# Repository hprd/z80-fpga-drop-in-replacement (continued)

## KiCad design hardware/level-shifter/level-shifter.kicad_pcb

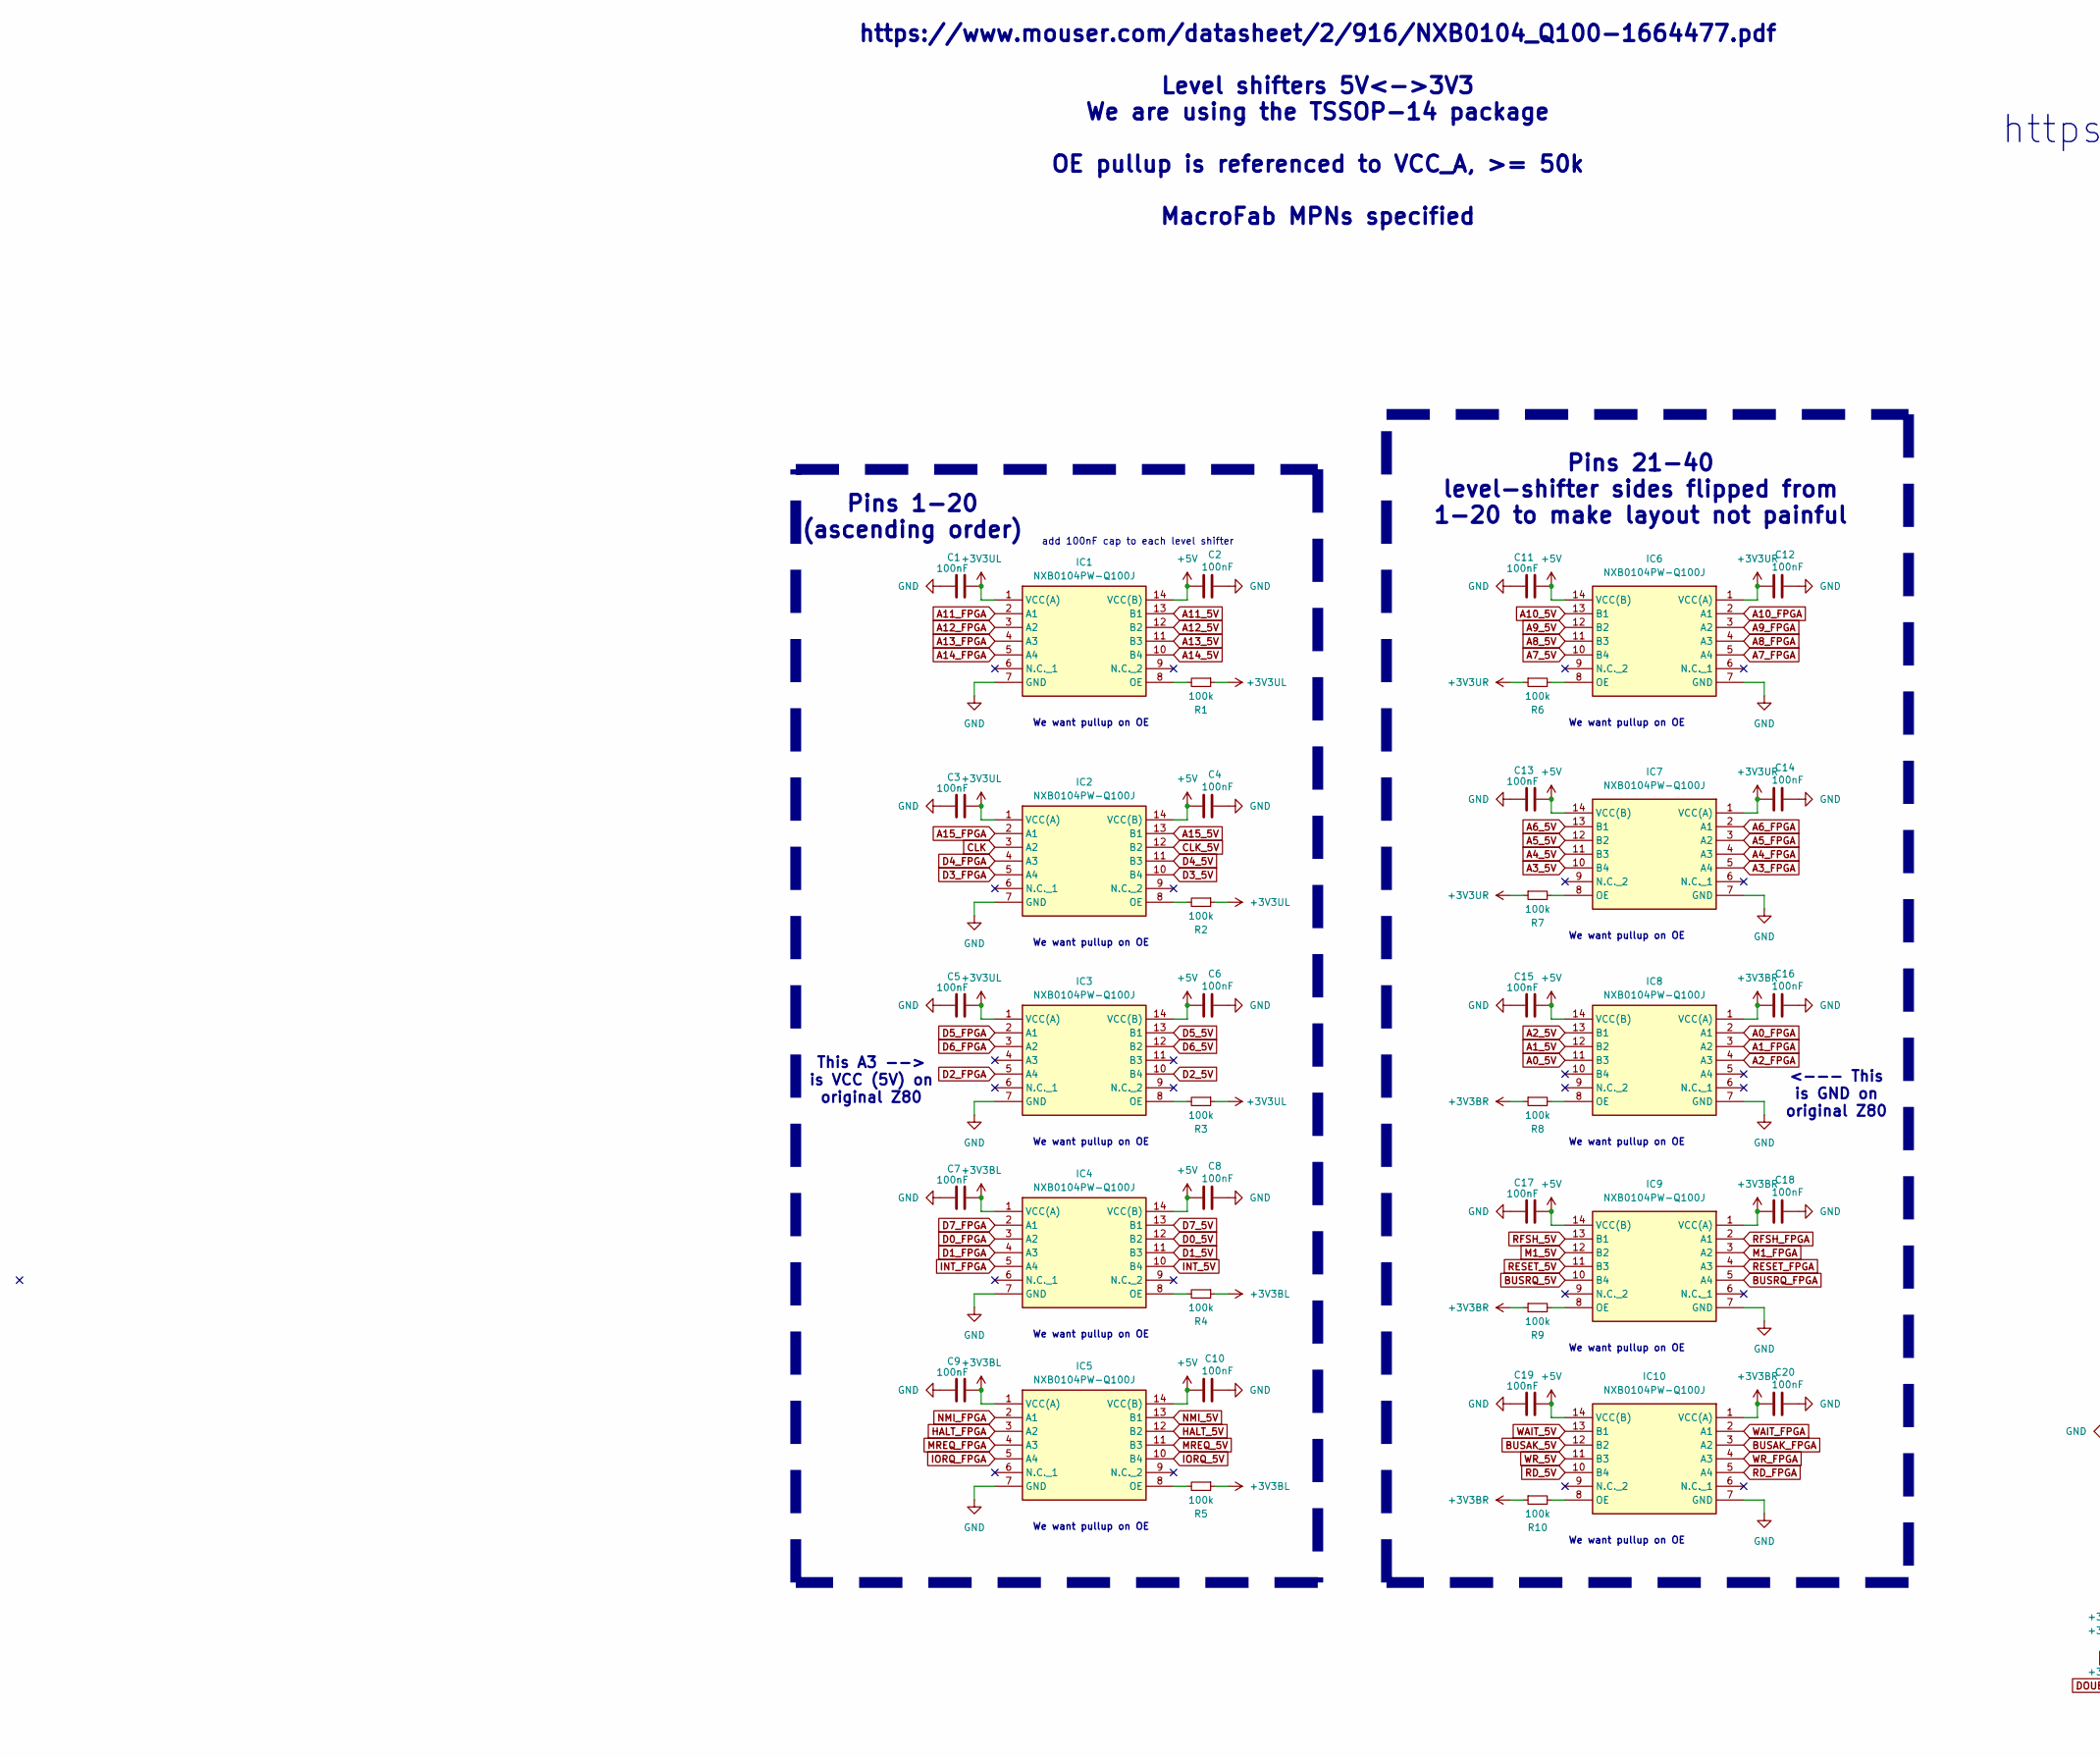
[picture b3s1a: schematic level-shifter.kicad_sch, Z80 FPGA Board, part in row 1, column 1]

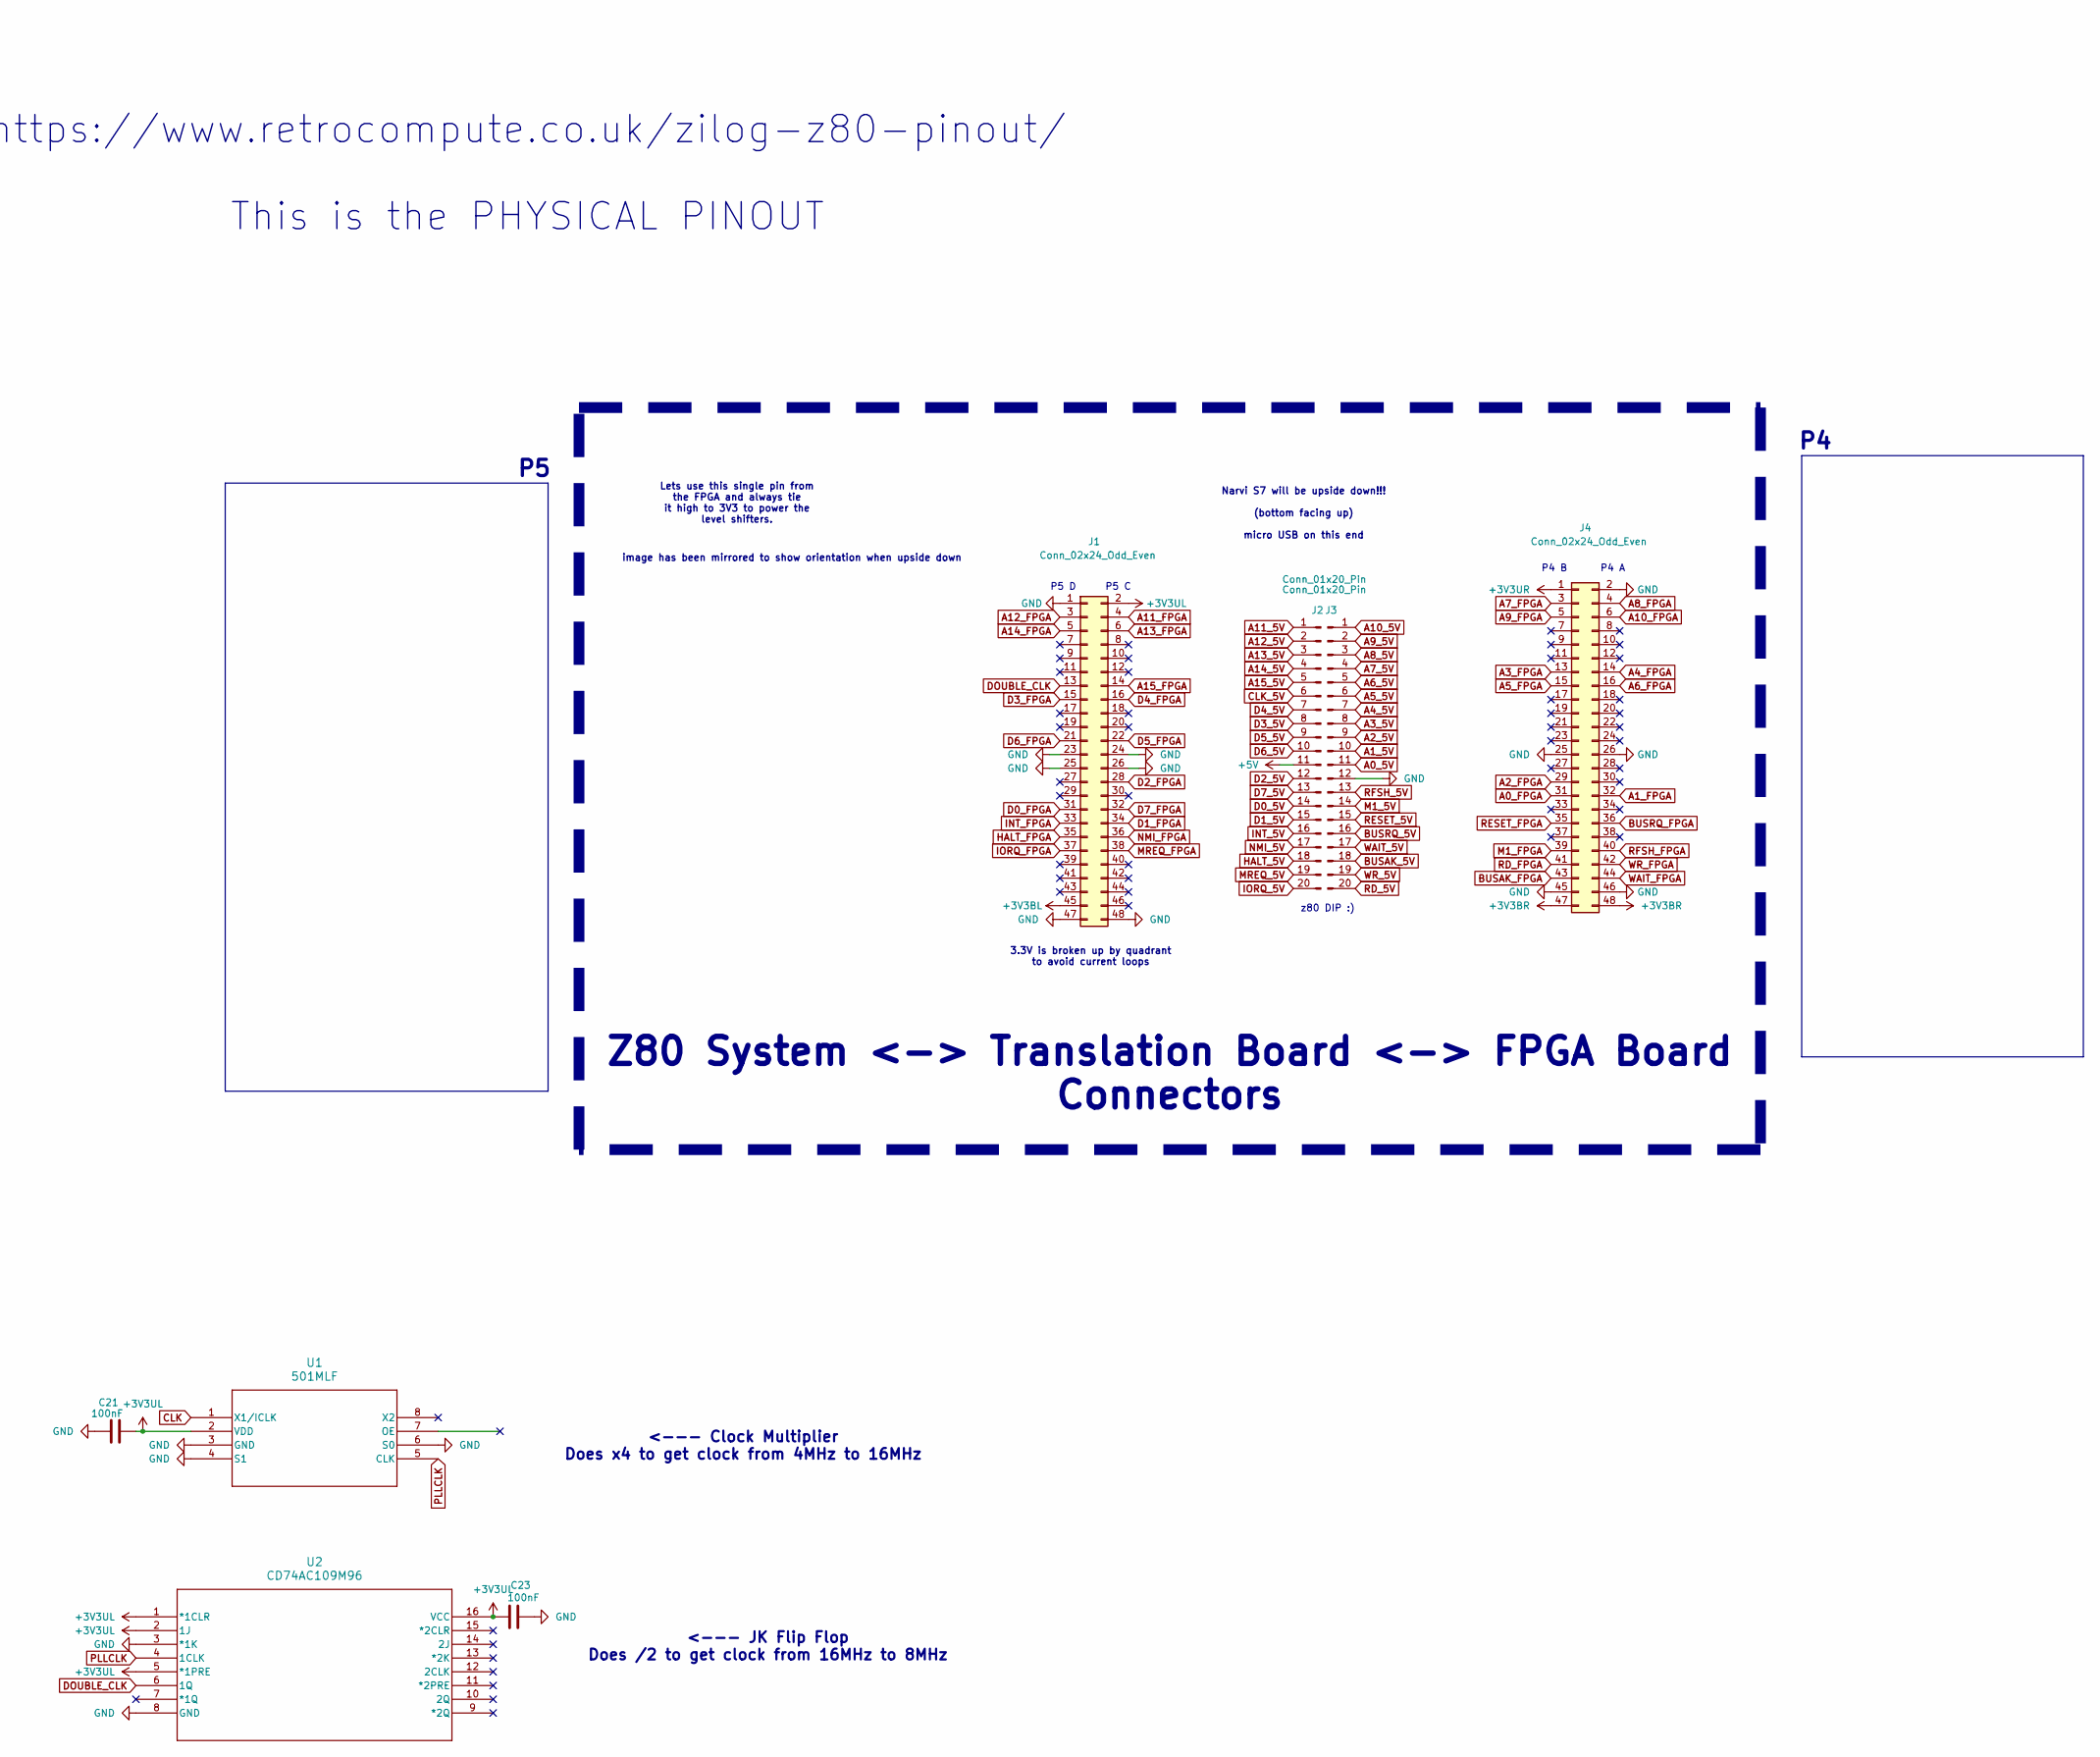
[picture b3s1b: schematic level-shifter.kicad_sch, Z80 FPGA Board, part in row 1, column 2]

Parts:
C1, C2, C3, C4, C5, C6, C7, C8, C9, C10, C11, C12, C13, C14, C15, C16, C17, C18, C19, C20, C21, C23: 100nF; C_0805_2012Metric
IC1, IC2, IC3, IC4, IC5, IC6, IC7, IC8, IC9, IC10: NXB0104PW-Q100J; SOP65P640X110-14N; Mouser Part Number 771-NXB0104PW-Q100J
J1, J4: Conn_02x24_Odd_Even; PinHeader_2x24_P2.54mm_Vertical
J2, J3: Conn_01x20_Pin; PinHeader_1x20_P2.54mm_Vertical
R1, R2, R3, R4, R5, R6, R7, R8, R9, R10: 100k; R_0805_2012Metric; MPN ERJ-UP6D6202V
U1: 501MLF; SOIC8_DCG8D1_REN
U2: CD74AC109M96

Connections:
+3V3BL: C7.2, C9.2, IC4.1 (VCC(A)), IC5.1 (VCC(A)), J1.45, R4.1, R5.1
+3V3BR: C16.1, C18.1, C20.1, IC8.1 (VCC(A)), IC9.1 (VCC(A)), IC10.1 (VCC(A)), J4.47, J4.48, R8.1, R9.1, R10.1
+3V3UL: C1.2, C3.2, C5.2, C21.2, C23.1, IC1.1 (VCC(A)), IC2.1 (VCC(A)), IC3.1 (VCC(A)), J1.2, R1.1, R2.1, R3.1, U1.2 (VDD), U2.1 (*1CLR), U2.2 (1J), U2.5 (*1PRE), U2.16 (VCC)
+3V3UR: C12.1, C14.1, IC6.1 (VCC(A)), IC7.1 (VCC(A)), J4.1, R6.1, R7.1
+5V: C2.1, C4.1, C6.1, C8.1, C10.1, C11.2, C13.2, C15.2, C17.2, C19.2, IC1.14 (VCC(B)), IC2.14 (VCC(B)), IC3.14 (VCC(B)), IC4.14 (VCC(B)), IC5.14 (VCC(B)), IC6.14 (VCC(B)), IC7.14 (VCC(B)), IC8.14 (VCC(B)), IC9.14 (VCC(B)), IC10.14 (VCC(B)), J2.11
A0_5V: IC8.11 (B3), J3.11
A0_FPGA: IC8.2 (A1), J4.31
A1_5V: IC8.12 (B2), J3.10
A1_FPGA: IC8.3 (A2), J4.32
A2_5V: IC8.13 (B1), J3.9
A2_FPGA: IC8.4 (A3), J4.29
A3_5V: IC7.10 (B4), J3.8
A3_FPGA: IC7.5 (A4), J4.13
A4_5V: IC7.11 (B3), J3.7
A4_FPGA: IC7.4 (A3), J4.14
A5_5V: IC7.12 (B2), J3.6
A5_FPGA: IC7.3 (A2), J4.15
A6_5V: IC7.13 (B1), J3.5
A6_FPGA: IC7.2 (A1), J4.16
A7_5V: IC6.10 (B4), J3.4
A7_FPGA: IC6.5 (A4), J4.3
A8_5V: IC6.11 (B3), J3.3
A8_FPGA: IC6.4 (A3), J4.4
A9_5V: IC6.12 (B2), J3.2
A9_FPGA: IC6.3 (A2), J4.5
A10_5V: IC6.13 (B1), J3.1
A10_FPGA: IC6.2 (A1), J4.6
A11_5V: IC1.13 (B1), J2.1
A11_FPGA: IC1.2 (A1), J1.4
A12_5V: IC1.12 (B2), J2.2
A12_FPGA: IC1.3 (A2), J1.3
A13_5V: IC1.11 (B3), J2.3
A13_FPGA: IC1.4 (A3), J1.6
A14_5V: IC1.10 (B4), J2.4
A14_FPGA: IC1.5 (A4), J1.5
A15_5V: IC2.13 (B1), J2.5
A15_FPGA: IC2.2 (A1), J1.14
BUSAK_5V: IC10.12 (B2), J3.18
BUSAK_FPGA: IC10.3 (A2), J4.43
BUSRQ_5V: IC9.10 (B4), J3.16
BUSRQ_FPGA: IC9.5 (A4), J4.36
CLK: IC2.3 (A2), U1.1 (X1/ICLK)
CLK_5V: IC2.12 (B2), J2.6
D0_5V: IC4.12 (B2), J2.14
D0_FPGA: IC4.3 (A2), J1.31
D1_5V: IC4.11 (B3), J2.15
D1_FPGA: IC4.4 (A3), J1.34
D2_5V: IC3.10 (B4), J2.12
D2_FPGA: IC3.5 (A4), J1.28
D3_5V: IC2.10 (B4), J2.8
D3_FPGA: IC2.5 (A4), J1.15
D4_5V: IC2.11 (B3), J2.7
D4_FPGA: IC2.4 (A3), J1.16
D5_5V: IC3.13 (B1), J2.9
D5_FPGA: IC3.2 (A1), J1.22
D6_5V: IC3.12 (B2), J2.10
D6_FPGA: IC3.3 (A2), J1.21
D7_5V: IC4.13 (B1), J2.13
D7_FPGA: IC4.2 (A1), J1.32
DOUBLE_CLK: J1.13, U2.6 (1Q)
GND: C1.1, C2.2, C3.1, C4.2, C5.1, C6.2, C7.1, C8.2, C9.1, C10.2, C11.1, C12.2, C13.1, C14.2, C15.1, C16.2, C17.1, C18.2, C19.1, C20.2, C21.1, C23.2, IC1.7 (GND), IC2.7 (GND), IC3.7 (GND), IC4.7 (GND), IC5.7 (GND), IC6.7 (GND), IC7.7 (GND), IC8.7 (GND), IC9.7 (GND), IC10.7 (GND), J1.1, J1.23, J1.24, J1.25, J1.26, J1.47, J1.48, J3.12, J4.2, J4.25, J4.26, J4.45, J4.46, U1.3 (GND), U1.4 (S1), U1.6 (S0), U2.3 (*1K), U2.8 (GND)
HALT_5V: IC5.12 (B2), J2.18
HALT_FPGA: IC5.3 (A2), J1.35
INT_5V: IC4.10 (B4), J2.16
INT_FPGA: IC4.5 (A4), J1.33
IORQ_5V: IC5.10 (B4), J2.20
IORQ_FPGA: IC5.5 (A4), J1.37
M1_5V: IC9.12 (B2), J3.14
M1_FPGA: IC9.3 (A2), J4.39
MREQ_5V: IC5.11 (B3), J2.19
MREQ_FPGA: IC5.4 (A3), J1.38
NMI_5V: IC5.13 (B1), J2.17
NMI_FPGA: IC5.2 (A1), J1.36
unnamed: IC1.8 (OE), R1.2
unnamed: IC2.8 (OE), R2.2
unnamed: IC3.8 (OE), R3.2
unnamed: IC4.8 (OE), R4.2
unnamed: IC5.8 (OE), R5.2
unnamed: IC6.8 (OE), R6.2
unnamed: IC7.8 (OE), R7.2
unnamed: IC8.8 (OE), R8.2
unnamed: IC9.8 (OE), R9.2
unnamed: IC10.8 (OE), R10.2
PLLCLK: U1.5 (CLK), U2.4 (1CLK)
RD_5V: IC10.10 (B4), J3.20
RD_FPGA: IC10.5 (A4), J4.41
RESET_5V: IC9.11 (B3), J3.15
RESET_FPGA: IC9.4 (A3), J4.35
RFSH_5V: IC9.13 (B1), J3.13
RFSH_FPGA: IC9.2 (A1), J4.40
WAIT_5V: IC10.13 (B1), J3.17
WAIT_FPGA: IC10.2 (A1), J4.44
WR_5V: IC10.11 (B3), J3.19
WR_FPGA: IC10.4 (A3), J4.42

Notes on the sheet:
https://www.retrocompute.co.uk/zilog-z80-pinout/ This is the PHYSICAL PINOUT
We want pullup on OE
P4 A
P5 C
Z80 System <-> Translation Board <-> FPGA Board Connectors
<--- JK Flip Flop Does /2 to get clock from 16MHz to 8MHz
P5 D
Pins 21-40 level-shifter sides flipped from 1-20 to make layout not painful
z80 DIP :)
3.3V is broken up by quadrant to avoid current loops
image has been mirrored to show orientation when upside down
Narvi S7 will be upside down!!! (bottom facing up) micro USB on this end
<--- Clock Multiplier Does x4 to get clock from 4MHz to 16MHz
https://www.mouser.com/datasheet/2/916/NXB0104_Q100-1664477.pdf Level shifters 5V<->3V3 We are using the TSSOP-14 package OE pullup is referenced to VCC_A, >= 50k MacroFab MPNs specified
add 100nF cap to each level shifter
This A3 --> is VCC (5V) on original Z80
Lets use this single pin from the FPGA and always tie it high to 3V3 to power the level shifters.
<--- This is GND on original Z80
P4 B
Pins 1-20 (ascending order)

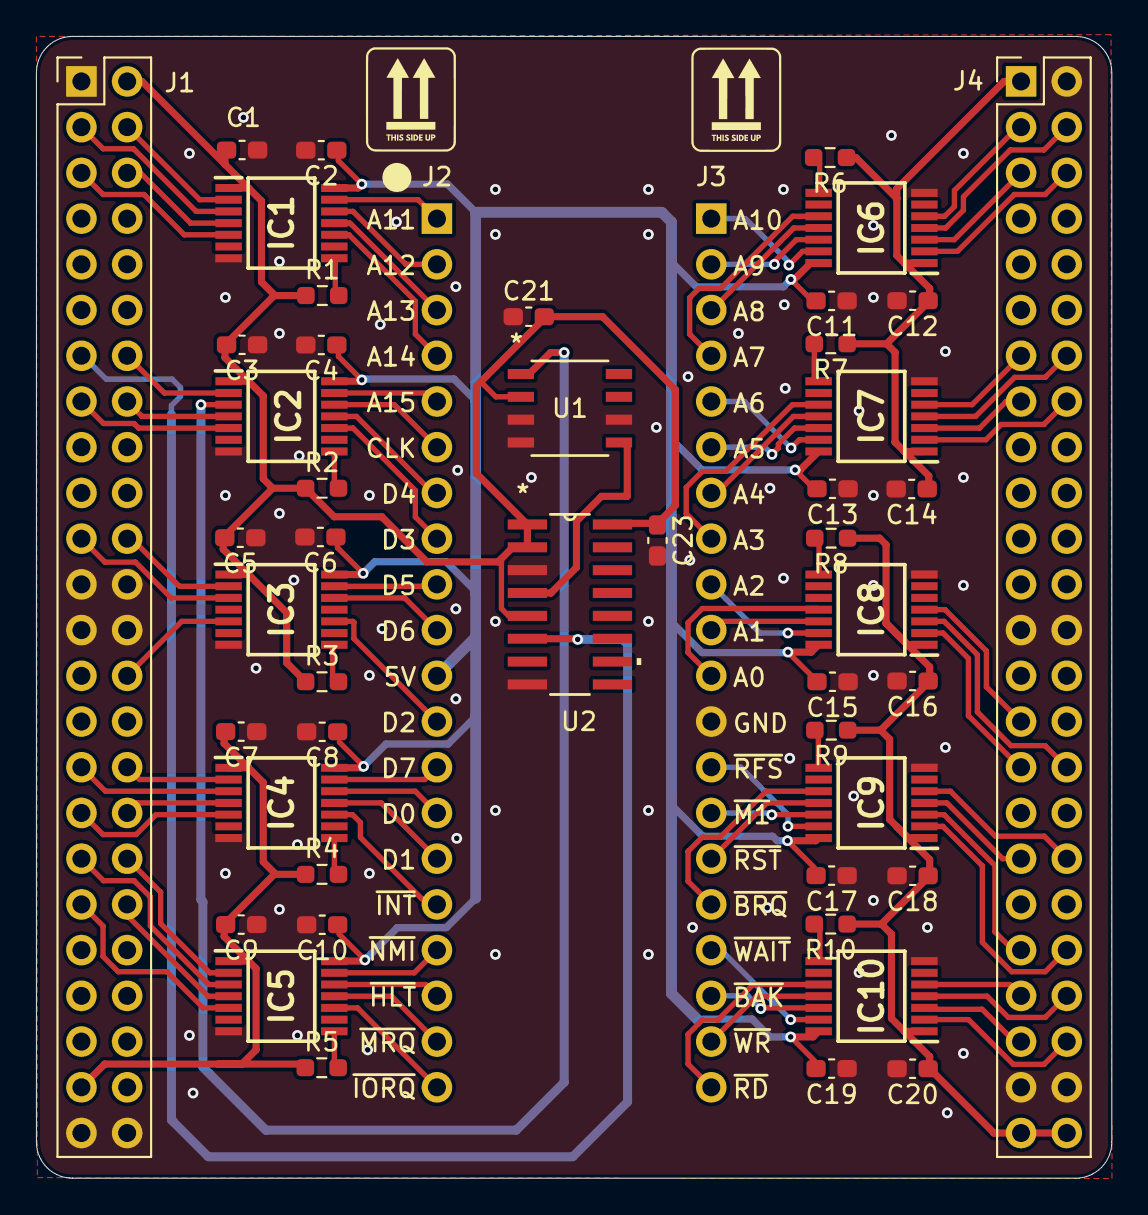
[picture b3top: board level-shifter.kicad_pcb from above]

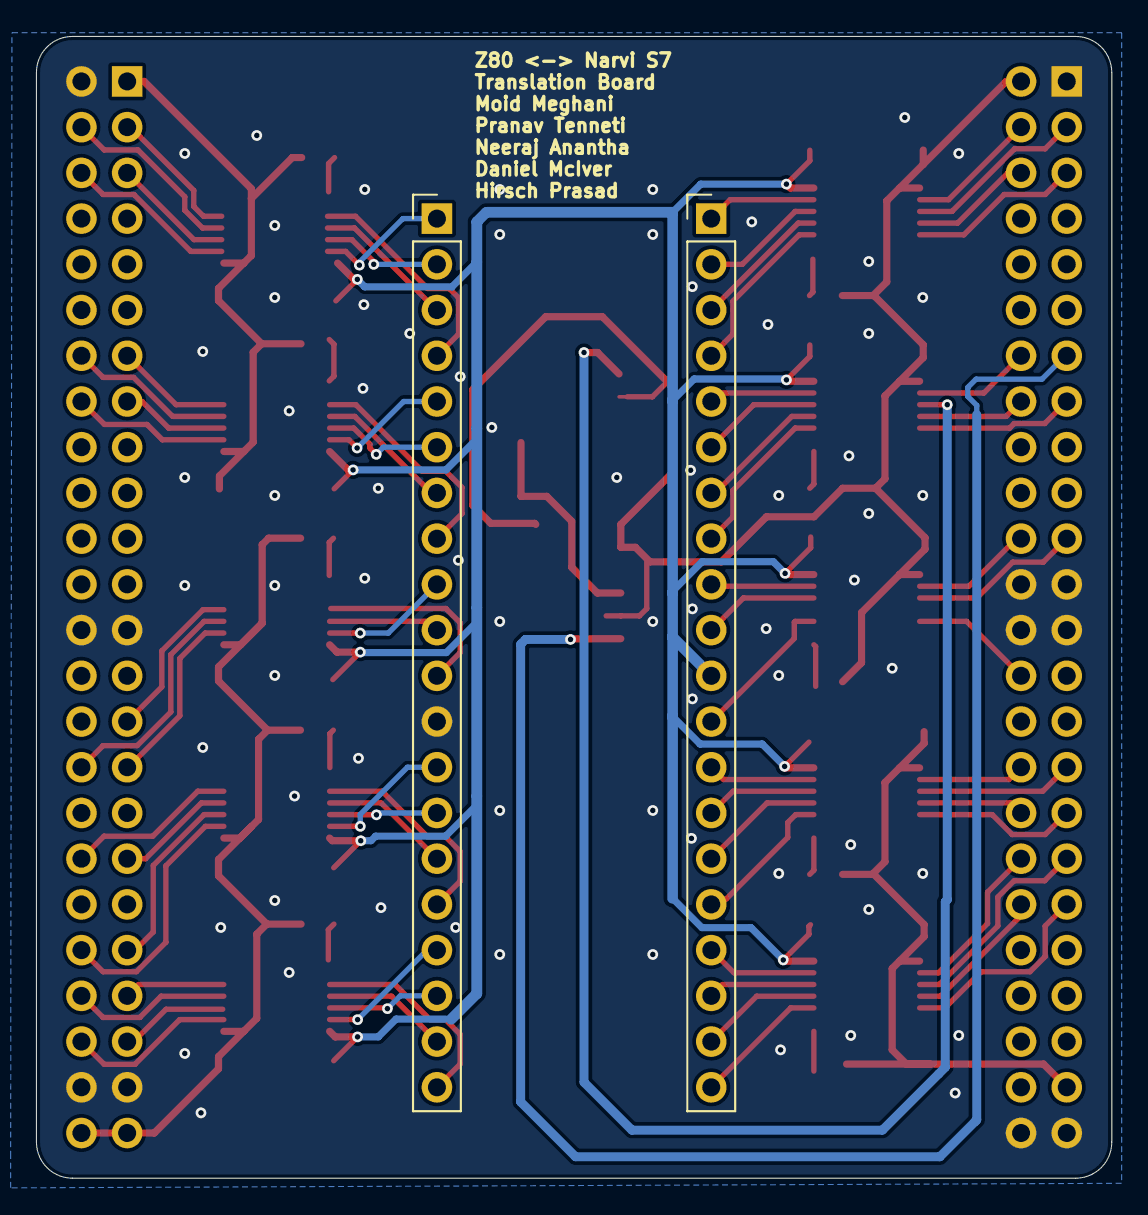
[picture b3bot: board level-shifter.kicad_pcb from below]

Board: 2 copper layers, 59.7 x 63.4 mm, 48 parts (2 on the bottom side), 94 nets.

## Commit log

2025-10-13 Adding previous team's documentation
2026-02-06 hardware push
2026-02-06 Working RTL for Basic LD, ADD, JP, and HALT program
2026-02-12 changed PCB to include FlipFlop
2026-02-12 updated timings and defines
2026-02-13 Should actually be synthesizable now
2026-02-20 Loaded that doug to memory
2026-02-23 cleaned up files
2026-02-23 added reset logic
2026-02-23 added assembler and assembly files
2026-02-24 OUT and XOR done
2026-02-24 fixed top_w_mem
2026-02-24 fixed OUT D and M1_b
2026-02-28 constraints for FPGA
2026-03-02 Hook 'Em Demo added
2026-03-04 added tester board files
2026-03-04 oscillator
2026-03-05 redoing clock for tester
2026-03-06 pcb stuff
2026-03-07 schematic done
2026-03-07 Finalize schematic changes, added archive for sharing project
2026-03-09 updated PCB to fix logic, ready to place and route
2026-03-19 minor changes to pcb : labels for schematic
2026-03-19 Cleared errors on schematic - superfluous enable signal
2026-03-20 Placed PCB awaiting review
2026-03-23 Almost done routing
2026-03-27 PCB routed no errors
2026-03-28 last silk screen labels added
2026-04-01 Dec, DJNZ, and JR group instructions
2026-04-01 coe files for new instructions
2026-04-21 Add files via upload
    Having a great struggle pushing for some reason so uploading zips for the final versions
2026-04-28 Final Code Before I Delete Vivado
